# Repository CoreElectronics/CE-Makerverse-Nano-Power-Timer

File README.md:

# Makerverse™ Nano Power Timer

This is the repo for the Core Electronics [Makerverse Nano Power Timer](https://core-electronics.com.au/catalog/product/view/sku/ce07927).

The PCB layout project requires KiCAD 5.99 or newer to view. The schematic and PCB are both provided in PDF format in the Documents folder.

## License
This project is open source - please review the LICENSE.md file for further licensing information.

If you have any technical questions, or concerns about licensing, please contact technical support on the [Core Electronics forums](https://forum.core-electronics.com.au/).

*\"PiicoDev\" and the PiicoDev logo are trademarks of Core Electronics Pty Ltd.*

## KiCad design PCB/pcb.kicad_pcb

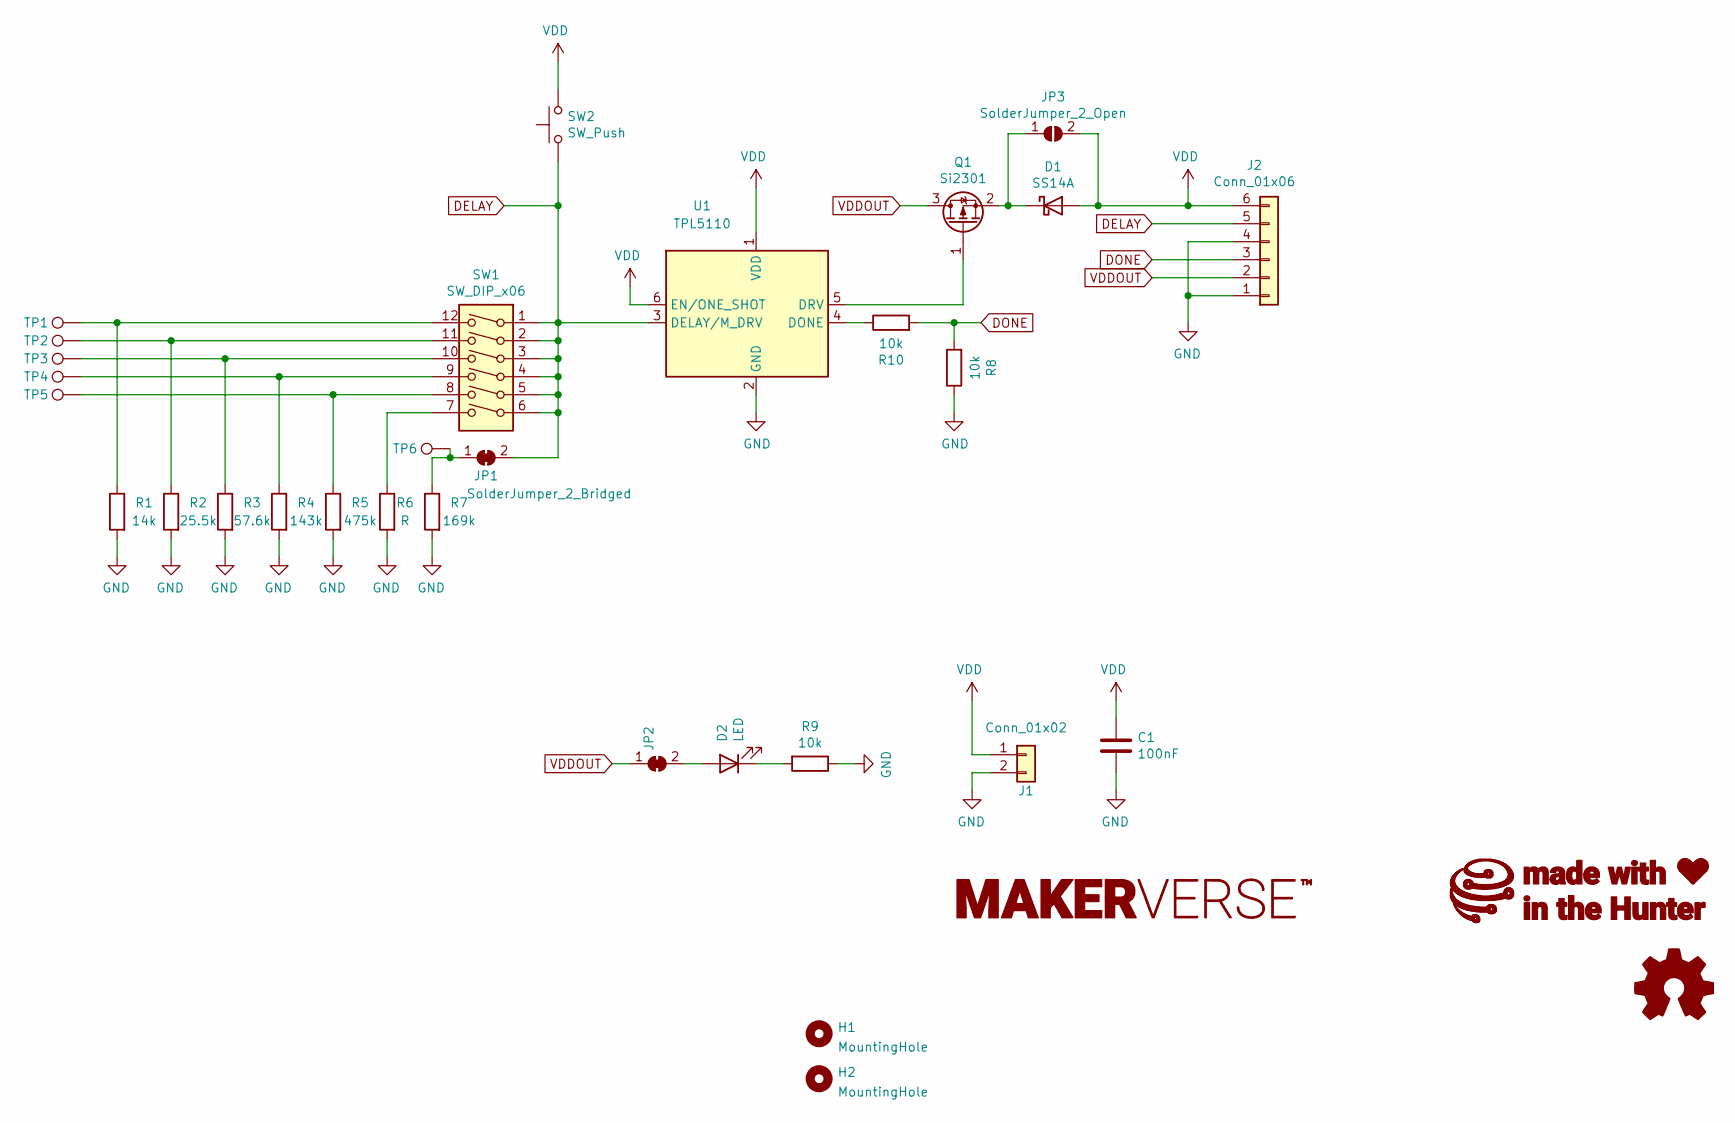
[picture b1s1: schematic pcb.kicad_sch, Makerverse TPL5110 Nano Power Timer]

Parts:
C1: 100nF; C_0402_1005Metric
D1: SS14A; D_SMA
D2: LED; LED_0603_1608Metric
G2: LOGO_CoreElectronics_made-with-love; CE07927
H1, H2: MountingHole; MountingHole_3.2mm_M3
J1: Conn_01x02; JST_PH_S2B-PH-SM4-TB_1x02-1MP_P2.00mm_Horizontal
J2: Conn_01x06; PinHeader_1x06_P2.54mm_Vertical
JP1, JP2: SolderJumper_2_Bridged; SolderJumper-2_P1.3mm_Bridged_RoundedPad1.0x1.5mm
JP3: SolderJumper_2_Open; SolderJumper-2_P1.3mm_Open_RoundedPad1.0x1.5mm_NoMask
Q1: Si2301; SOT-23
R1: 14k; R_0402_1005Metric
R2: 25.5k; R_0402_1005Metric
R3: 57.6k; R_0402_1005Metric
R4: 143k; R_0402_1005Metric
R5: 475k; R_0402_1005Metric
R6: R; R_Axial_DIN0207_L6.3mm_D2.5mm_P7.62mm_Horizontal
R7: 169k; R_0402_1005Metric
R8, R9, R10: 10k; R_0402_1005Metric
SW1: SW_DIP_x06; SW_DIP_SPSTx06_Slide_6.7x16.8mm_W8.61mm_P2.54mm_LowProfile
SW2: SW_Push; SW_SPST_TL3305A
TP1, TP2, TP3, TP4, TP5, TP6: TestPoint; TestPoint_THTPad_D1.5mm_Drill0.7mm
U1: TPL5110; SOT-23-6

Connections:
DELAY: J2.5, JP1.2 (B), SW1.1, SW1.2, SW1.3, SW1.4, SW1.5, SW1.6, SW2.1, U1.3 (DELAY/M_DRV)
DONE: J2.3, R8.2, R10.2
GND: C1.2, J1.2, J2.1, J2.4, R1.2, R2.2, R3.2, R4.2, R5.2, R6.2, R7.2, R8.1, R9.1, U1.2 (GND)
unnamed: D1.1 (K), JP3.1 (A), Q1.2 (S)
unnamed: D2.1 (K), R9.2
unnamed: D2.2 (A), JP2.2 (B)
unnamed: JP1.1 (A), R7.1, TP6.1
unnamed: Q1.1 (G), U1.5 (DRV)
unnamed: R1.1, SW1.12, TP1.1
unnamed: R2.1, SW1.11, TP2.1
unnamed: R3.1, SW1.10, TP3.1
unnamed: R4.1, SW1.9, TP4.1
unnamed: R5.1, SW1.8, TP5.1
unnamed: R6.1, SW1.7
unnamed: R10.1, U1.4 (DONE)
VDD: C1.1, D1.2 (A), J1.1, J2.6, JP3.2 (B), SW2.2, U1.1 (VDD), U1.6 (EN/ONE_SHOT)
VDDOUT: J2.2, JP2.1 (A), Q1.3 (D)

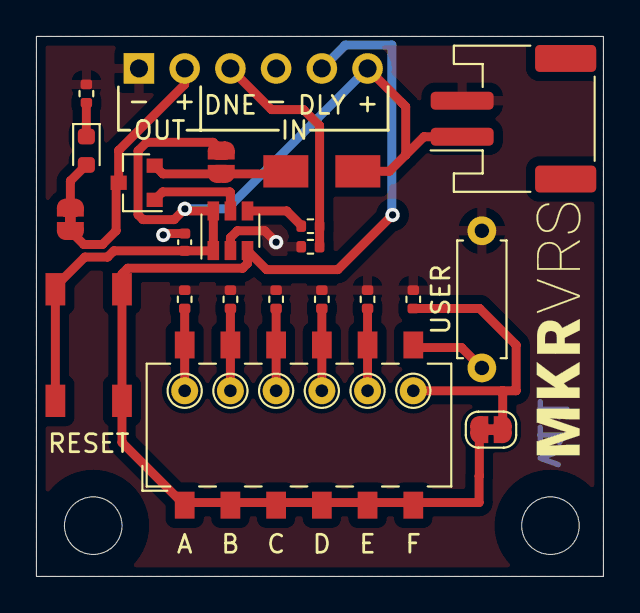
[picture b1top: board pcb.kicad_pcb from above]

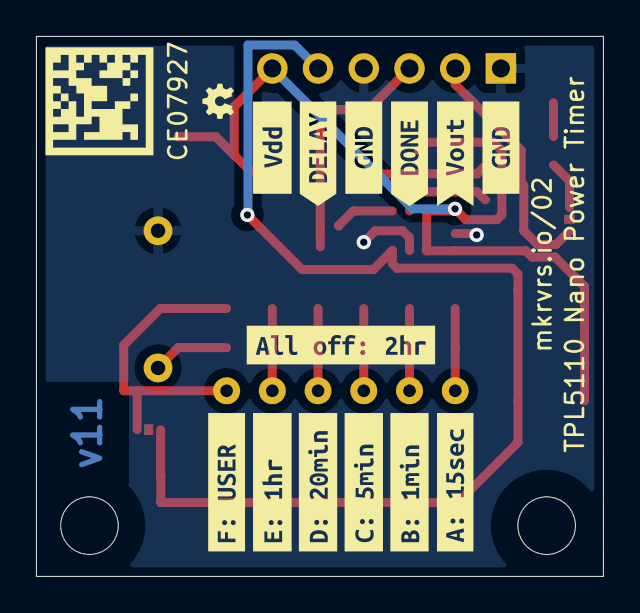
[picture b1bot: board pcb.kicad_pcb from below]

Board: 2 copper layers, 31.5 x 30.0 mm, 44 parts (14 on the bottom side), 17 nets.

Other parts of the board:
kibuzzard-6108B5D9: G***; kibuzzard-6108B5D9
kibuzzard-6108B5E5: G***; kibuzzard-6108B5E5
kibuzzard-6108B5F6: G***; kibuzzard-6108B5F6
kibuzzard-6108B610: G***; kibuzzard-6108B610
kibuzzard-6108B621: G***; kibuzzard-6108B621
kibuzzard-6108B648: G***; kibuzzard-6108B648
kibuzzard-6108C156: G***; kibuzzard-6108C156
kibuzzard-6115C8A3: G***; kibuzzard-6115C8A3
kibuzzard-6115C8BC: G***; kibuzzard-6115C8BC
kibuzzard-6115C8D1: G***; kibuzzard-6115C8D1
kibuzzard-6115CA83: G***; kibuzzard-6115CA83
kibuzzard-6115CAE5: G***; kibuzzard-6115CAE5
kibuzzard-6115CB14: G***; kibuzzard-6115CB14

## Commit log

2021-12-07 Initial commit.
2021-12-07 Pre-Publish commit.

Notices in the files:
PCB/pcb.kicad_pcb:
License: CCASAv4.0 https://creativecommons.org/licenses/by-sa/4.0
